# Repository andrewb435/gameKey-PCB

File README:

gameKey PCBs

This repo contains the main control board and thumb cluster board for gameKey devices.

The main board provides headers for a SparkFun Pro Micro to break into a diode key matrix, the analog inputs for the thumbstick, a mode switch (NYI), addressable LED (NeoPixel, WS2811, etc) (NYI), and a hardware kill switch to allow reflashing in case of some kind of firmware problem. It can either be hand assembled with 30x SOD-323 1n4148 diodes or ordered with PCB Assembly from JLCPCB (recommended).

The thumb cluster PCB is very simple, acting as a backing board and breakout for the navigation switch and joystick.

Main PCB Wiring
**The Enable header MUST be populated and shorted with a jumper to enable the firmware to output anything.**

The addressable LED will only work if you are using a 5V/16MHz Pro Micro. D is the Data pin, 5V is in the center, and GND is on the - label.

Each finger goes to it's nearest pads, with side buttons going to C5 in either configuration. Buttons are assigned from closest to the palm [R0] out to the end of the nuckle[R4], in order.

In the 'standard' configuration, used by your left hand, Pinky is on C0, Ring is on C1, Middle is on C2, Index is on C3, Nav Switch is on C4, and Index[R0]/Pinky[R1] Sides/Joystick push[R2]/Thumb Side[R3] buttons are on C5.

In the 'mirrored' configuration, used by your right hand, Pinky is on C4, Ring is on C3, Middle is on C2, Index is on C1, Nav Switch is on C0, and Index[R0]/Pinky[R1] Sides/Joystick push[R2]/Thumb Side[R3] buttons are on C5.

Thumb Cluster PCB
NavSwitch is wired to the Main Control in the order N[R0], E[R1], S[R2], W[R3], Push[R4] as labeled on the Thumb Cluster PCB.

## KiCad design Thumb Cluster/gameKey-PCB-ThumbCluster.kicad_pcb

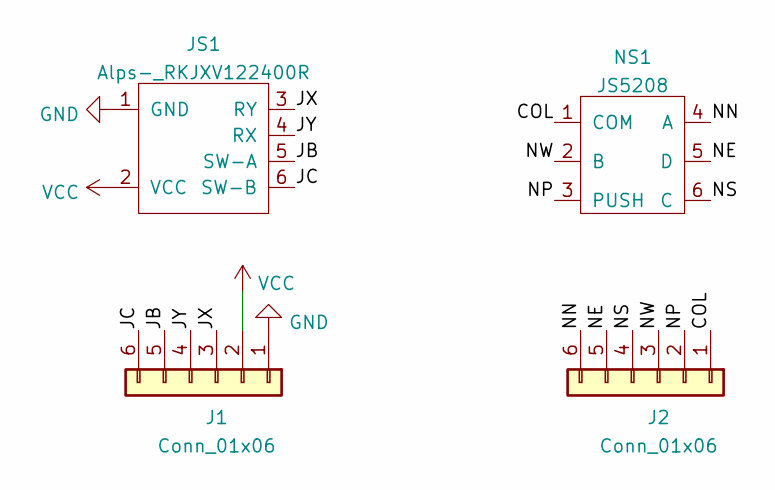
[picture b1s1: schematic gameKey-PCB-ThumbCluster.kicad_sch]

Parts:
J1, J2: Conn_01x06; PinHeader_1x06_P2.00mm_Vertical_SMD_Pin1Left
JS1: Alps-_RKJXV122400R; Alps-RKJXV1224
NS1: JS5208

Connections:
/COL: J2.1, NS1.1 (COM)
/JB: J1.5, JS1.5 (SW-A)
/JC: J1.6, JS1.6 (SW-B)
/JX: J1.3, JS1.3 (RY)
/JY: J1.4, JS1.4 (RX)
/NE: J2.5, NS1.5 (D)
/NN: J2.6, NS1.4 (A)
/NP: J2.2, NS1.3 (PUSH)
/NS: J2.4, NS1.6 (C)
/NW: J2.3, NS1.2 (B)
GND: J1.1, JS1.1 (GND)
VCC: J1.2, JS1.2 (VCC)

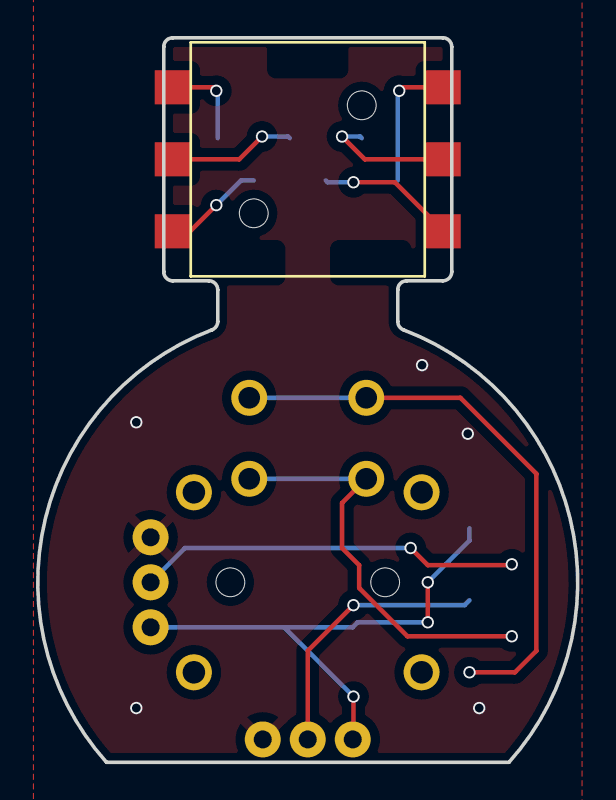
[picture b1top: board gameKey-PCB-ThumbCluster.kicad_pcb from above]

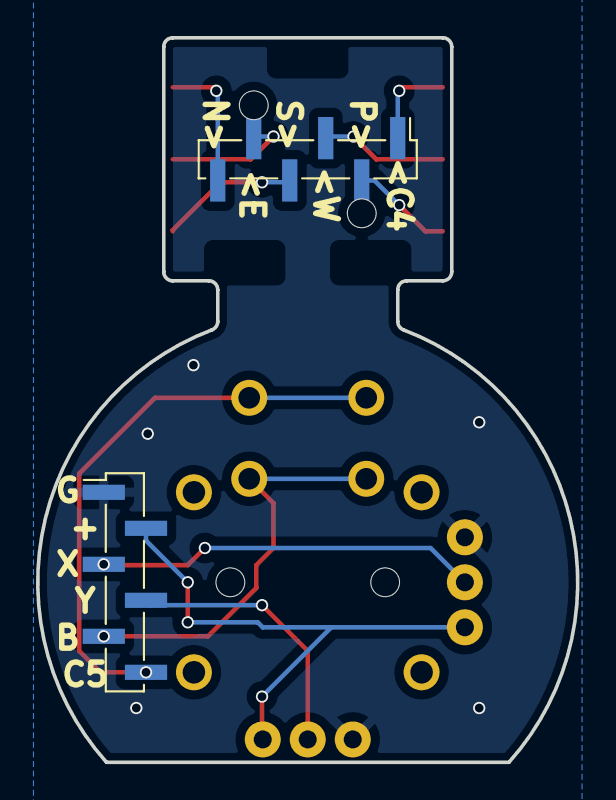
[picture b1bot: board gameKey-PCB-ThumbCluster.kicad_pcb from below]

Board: 2 copper layers, 30.0 x 40.2 mm, 4 parts (2 on the bottom side), 12 nets.

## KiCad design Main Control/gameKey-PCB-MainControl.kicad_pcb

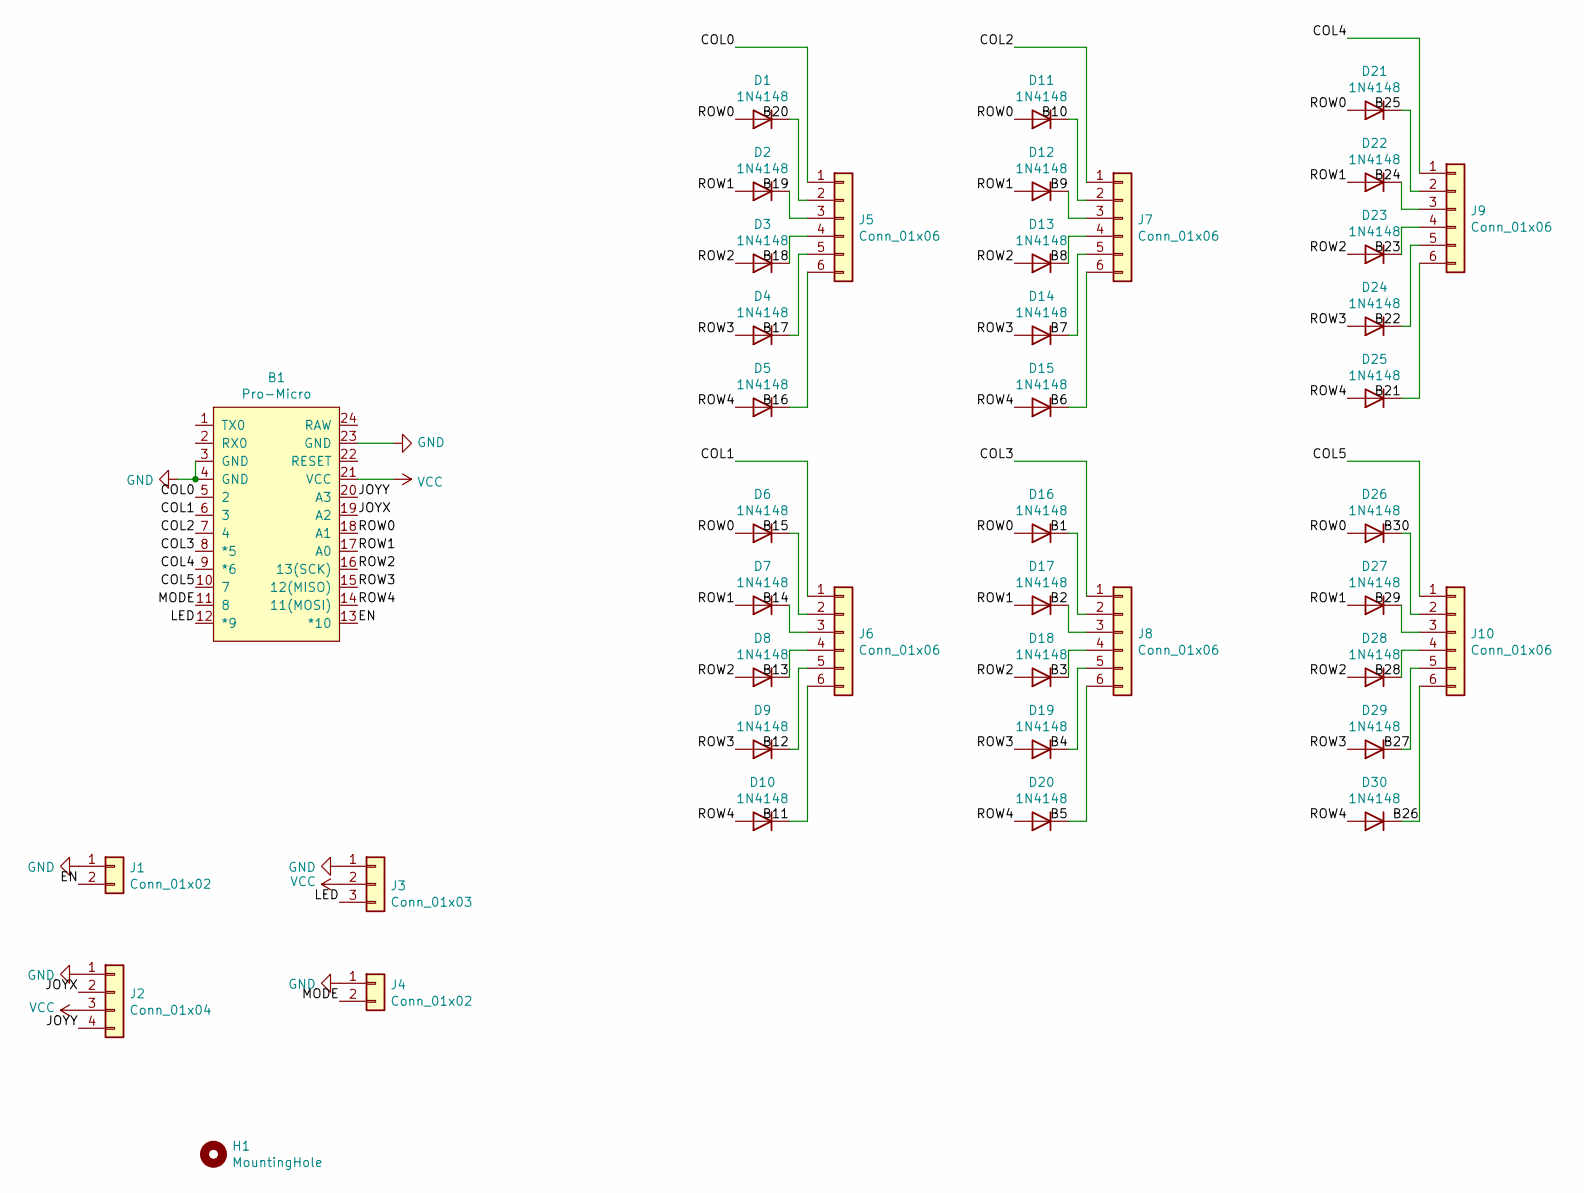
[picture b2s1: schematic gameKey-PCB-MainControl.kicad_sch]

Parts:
B1: Pro-Micro
D1, D2, D3, D4, D5, D6, D7, D8, D9, D10, D11, D12, D13, D14, D15, D16, D17, D18, D19, D20, D21, D22, D23, D24, D25, D26, D27, D28, D29, D30: 1N4148; D_SOD-323F; LCSC C2128
H1: MountingHole; MountingHole_2.2mm_M2_ISO7380
J1, J4: Conn_01x02; PinHeader_1x02_P2.54mm_Vertical
J2: Conn_01x04; PinSocket_1x04_P2.00mm_Vertical_SMD_Pin1Left
J3: Conn_01x03; PinHeader_1x03_P2.54mm_Vertical
J5, J6, J7, J8, J9, J10: Conn_01x06; SMD_PadLine_1x06

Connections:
/B1: D16.1 (K), J8.2
/B2: D17.1 (K), J8.3
/B3: D18.1 (K), J8.4
/B4: D19.1 (K), J8.5
/B5: D20.1 (K), J8.6
/B6: D15.1 (K), J7.6
/B7: D14.1 (K), J7.5
/B8: D13.1 (K), J7.4
/B9: D12.1 (K), J7.3
/B10: D11.1 (K), J7.2
/B11: D10.1 (K), J6.6
/B12: D9.1 (K), J6.5
/B13: D8.1 (K), J6.4
/B14: D7.1 (K), J6.3
/B15: D6.1 (K), J6.2
/B16: D5.1 (K), J5.6
/B17: D4.1 (K), J5.5
/B18: D3.1 (K), J5.4
/B19: D2.1 (K), J5.3
/B20: D1.1 (K), J5.2
/B21: D25.1 (K), J9.6
/B22: D24.1 (K), J9.5
/B23: D23.1 (K), J9.4
/B24: D22.1 (K), J9.3
/B25: D21.1 (K), J9.2
/B26: D30.1 (K), J10.6
/B27: D29.1 (K), J10.5
/B28: D28.1 (K), J10.4
/B29: D27.1 (K), J10.3
/B30: D26.1 (K), J10.2
/COL0: B1.5 (2), J5.1
/COL1: B1.6 (3), J6.1
/COL2: B1.7 (4), J7.1
/COL3: B1.8 (*5), J8.1
/COL4: B1.9 (*6), J9.1
/COL5: B1.10 (7), J10.1
/EN: B1.13 (*10), J1.2
/JOYX: B1.19 (A2), J2.2
/JOYY: B1.20 (A3), J2.4
/LED: B1.12 (*9), J3.3
/MODE: B1.11 (8), J4.2
/ROW0: B1.18 (A1), D1.2 (A), D6.2 (A), D11.2 (A), D16.2 (A), D21.2 (A), D26.2 (A)
/ROW1: B1.17 (A0), D2.2 (A), D7.2 (A), D12.2 (A), D17.2 (A), D22.2 (A), D27.2 (A)
/ROW2: B1.16 (13(SCK)), D3.2 (A), D8.2 (A), D13.2 (A), D18.2 (A), D23.2 (A), D28.2 (A)
/ROW3: B1.15 (12(MISO)), D4.2 (A), D9.2 (A), D14.2 (A), D19.2 (A), D24.2 (A), D29.2 (A)
/ROW4: B1.14 (11(MOSI)), D5.2 (A), D10.2 (A), D15.2 (A), D20.2 (A), D25.2 (A), D30.2 (A)
GND: B1.3 (GND), B1.4 (GND), B1.23 (GND), J1.1, J2.1, J3.1, J4.1
VCC: B1.21 (VCC), J2.3, J3.2

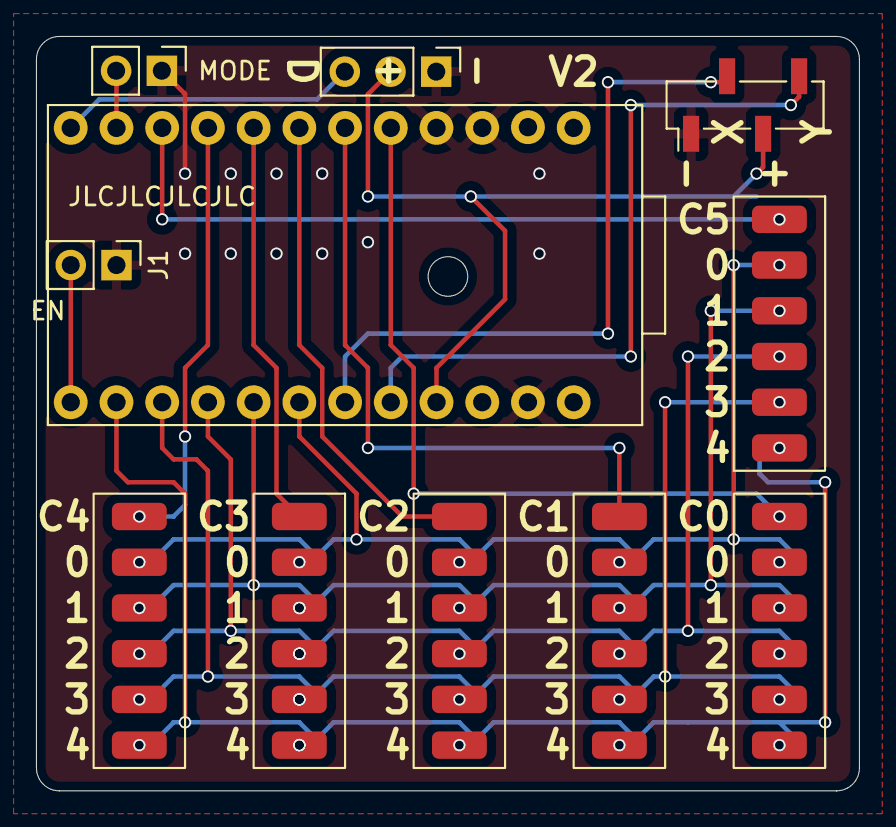
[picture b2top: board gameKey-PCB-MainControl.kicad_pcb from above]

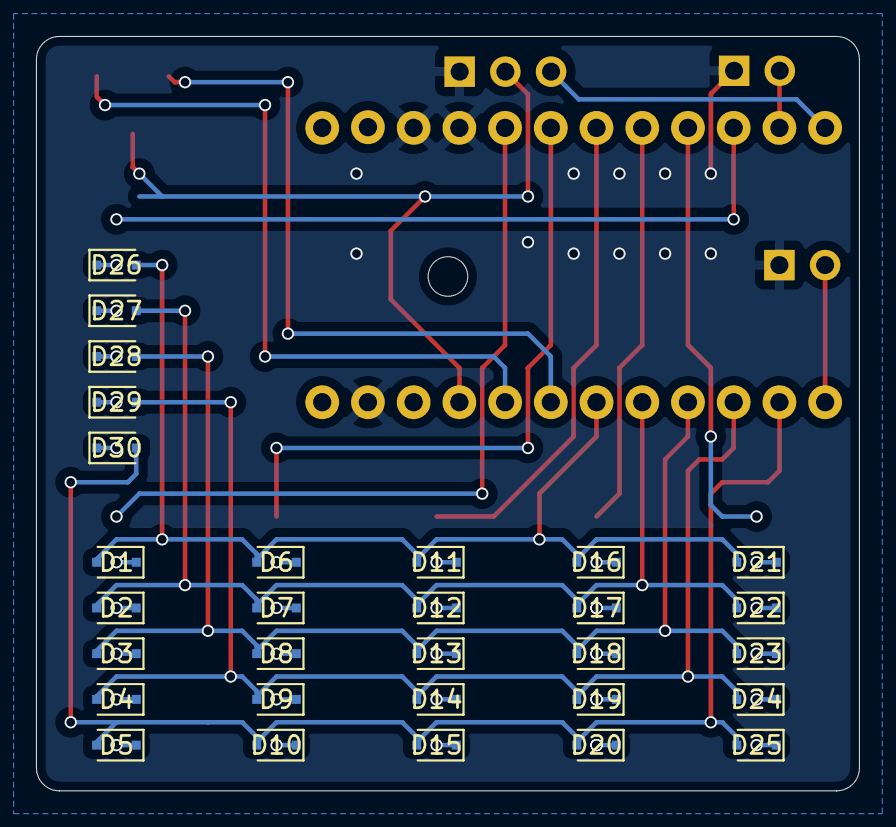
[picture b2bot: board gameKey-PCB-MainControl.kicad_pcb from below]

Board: 2 copper layers, 45.7 x 41.9 mm, 42 parts (30 on the bottom side), 48 nets.

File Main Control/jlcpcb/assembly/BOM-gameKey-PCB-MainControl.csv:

Comment,Designator,Footprint,LCSC
1N4148,"D1,D10,D11,D12,D13,D14,D15,D16,D17,D18,D19,D2,D20,D21,D22,D23,D24,D25,D26,D27,D28,D29,D3,D30,D4,D5,D6,D7,D8,D9",D_SOD-323F,C2128

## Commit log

2022-02-08 Add JLCPCB production files for ThumbCluster
2022-03-07 Update README Move images to doc
2023-02-22 Update README.md with part numbers
2023-09-06 Critical - thumb nav switch was missing column pin Broke out away from common ground and improved labeling
2023-09-06 Clarify thumb cluster column silkscreens
2025-03-02 Add Main Control - Schematic.pdf and Thumb Cluster - Schematic.pdf
